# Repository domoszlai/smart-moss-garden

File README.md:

# smart-moss-garden

https://www.youtube.com/watch?v=s0qQqOkIP7w

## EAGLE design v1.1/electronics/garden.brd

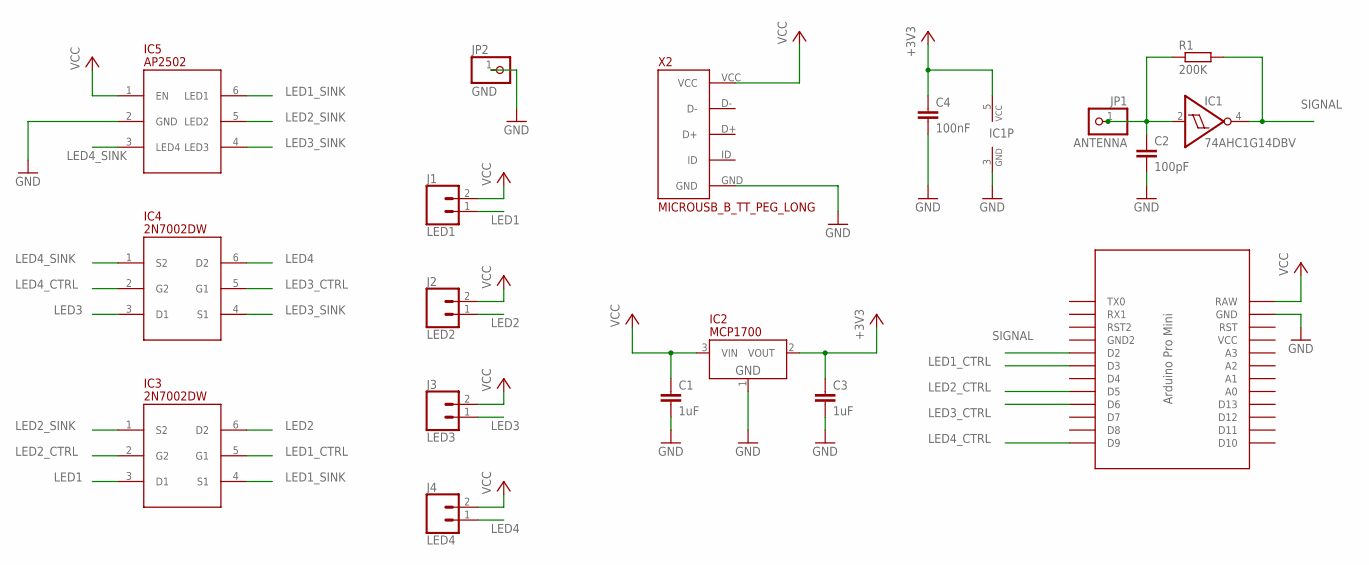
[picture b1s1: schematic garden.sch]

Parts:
C1, C3: 1uF; C0805
C2: 100pF; C0805
C4: 100nF; C0805
IC1: 74AHC1G14DBV; SOT23-5
IC2: MCP1700; SOT-23
IC3, IC4: 2N7002DW; SOT363
IC5: AP2502; SOT-23-6
J1: LED1; 1X02
J2: LED2; 1X02
J3: LED3; 1X02
J4: LED4; 1X02
JP1: ANTENNA; 1X01
JP2: GND; 1X01
R1: 200K; R0805
U$1: PRO-MINI-TWO-SIDES-ONLY
X2: MICROUSB_B_TT_PEG_LONG

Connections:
+3V3: C3.1, C4.1, IC1.5 (VCC), IC2.2 (VOUT)
ANTENNA: C2.1, IC1.2 (I), JP1.1, R1.1
GND: C1.2, C2.2, C3.2, C4.2, IC1.3 (GND), IC2.1 (GND), IC5.2 (GND), JP2.1, U$1.GND, X2.GND
LED1: IC3.3 (D1), J1.1
LED1_CTRL: IC3.5 (G1), U$1.D3
LED1_SINK: IC3.4 (S1), IC5.6 (LED1)
LED2: IC3.6 (D2), J2.1
LED2_CTRL: IC3.2 (G2), U$1.D5
LED2_SINK: IC3.1 (S2), IC5.5 (LED2)
LED3: IC4.3 (D1), J3.1
LED3_CTRL: IC4.5 (G1), U$1.D6
LED3_SINK: IC4.4 (S1), IC5.4 (LED3)
LED4: IC4.6 (D2), J4.1
LED4_CTRL: IC4.2 (G2), U$1.D9
LED4_SINK: IC4.1 (S2), IC5.3 (LED4)
SIGNAL: IC1.4 (O), R1.2, U$1.D2
VCC: C1.1, IC2.3 (VIN), IC5.1 (EN), J1.2, J2.2, J3.2, J4.2, U$1.RAW, X2.VCC

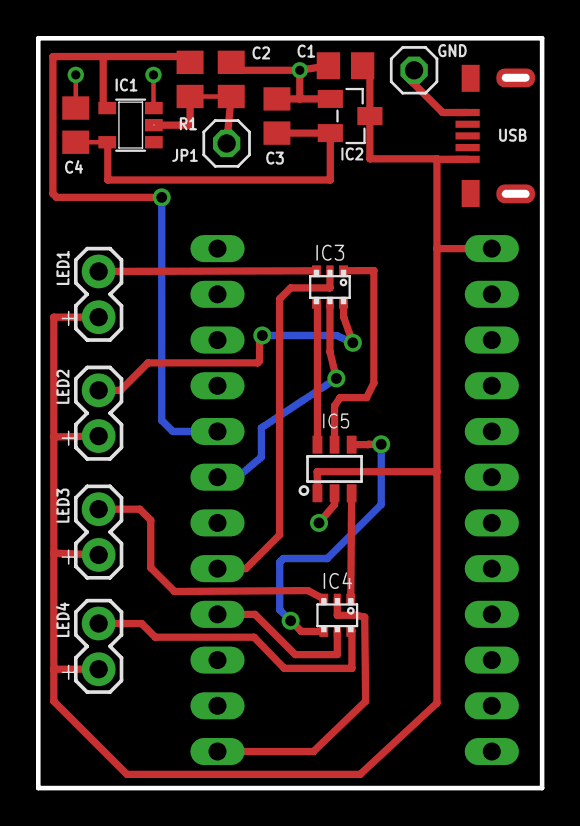
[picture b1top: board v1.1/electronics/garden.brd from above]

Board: 2 copper layers, 27.8 x 41.5 mm, 18 parts (0 on the bottom side), 17 nets.

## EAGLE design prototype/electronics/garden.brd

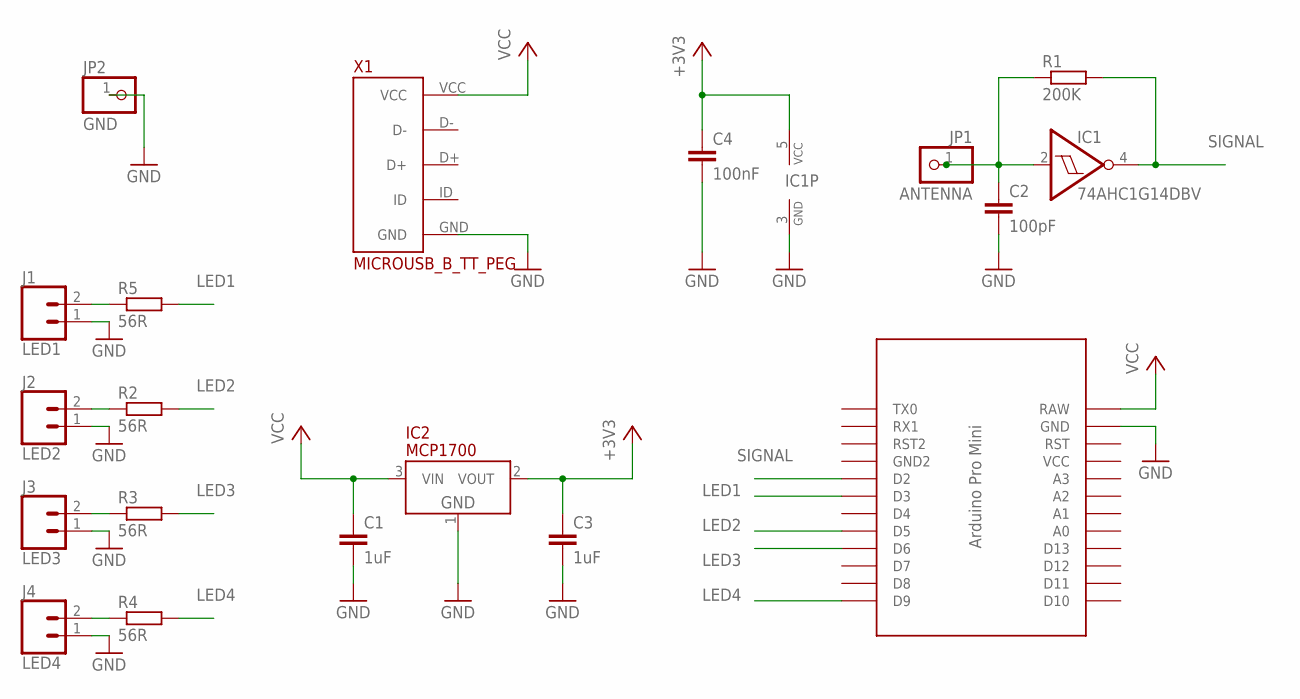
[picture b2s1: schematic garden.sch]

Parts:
C1, C3: 1uF; C0805
C2: 100pF; C0805
C4: 100nF; C0805
IC1: 74AHC1G14DBV; SOT23-5
IC2: MCP1700; SOT-23
J1: LED1; 1X02
J2: LED2; 1X02
J3: LED3; 1X02
J4: LED4; 1X02
JP1: ANTENNA; 1X01
JP2: GND; 1X01
R1: 200K; R0805
R2, R3, R4, R5: 56R; M0805
U$1: PRO-MINI-TWO-SIDES-ONLY
X1: MICROUSB_B_TT_PEG

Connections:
+3V3: C3.1, C4.1, IC1.5 (VCC), IC2.2 (VOUT)
ANTENNA: C2.1, IC1.2 (I), JP1.1, R1.1
GND: C1.2, C2.2, C3.2, C4.2, IC1.3 (GND), IC2.1 (GND), J1.1, J2.1, J3.1, J4.1, JP2.1, U$1.GND, X1.GND
LED1: R5.2, U$1.D3
LED2: R2.2, U$1.D5
LED3: R3.2, U$1.D6
LED4: R4.2, U$1.D9
unnamed: J1.2, R5.1
unnamed: J2.2, R2.1
unnamed: J3.2, R3.1
unnamed: J4.2, R4.1
SIGNAL: IC1.4 (O), R1.2, U$1.D2
VCC: C1.1, IC2.3 (VIN), U$1.RAW, X1.VCC

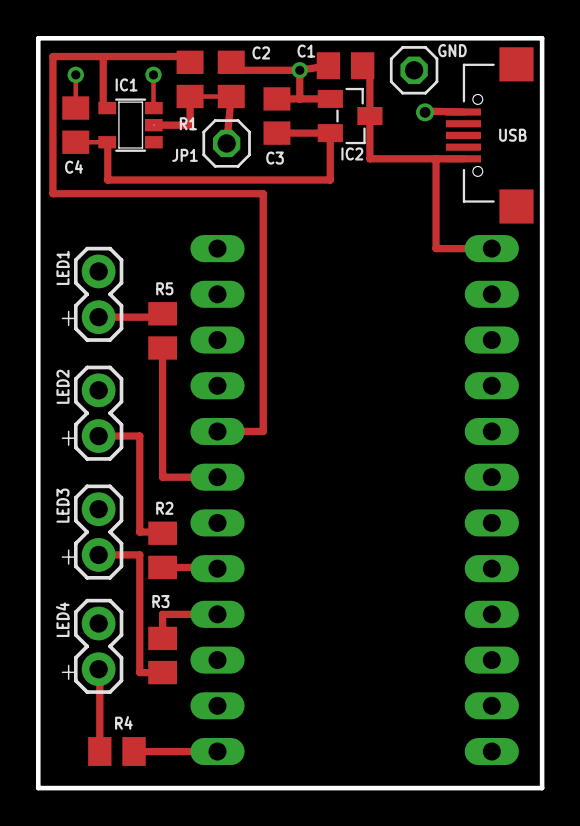
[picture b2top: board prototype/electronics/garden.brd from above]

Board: 2 copper layers, 28.0 x 41.7 mm, 19 parts (0 on the bottom side), 13 nets.

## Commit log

2017-03-25 the electronics design and the firmware for the prototype
2017-03-26 add box design from 2mm/3mm perplex
2017-07-14 1.0 schematics
2017-07-14 fix pinout
2017-08-25 v1.0 board
2017-08-27 ground plane isolation to 12mil
2017-08-27 add gerber files
2017-11-29 add latest electronics
2017-11-29 add schematics as PDF
2017-12-28 Add USB layout
2017-12-28 fix typo
2017-12-28 v1.1
2017-12-28 save progress in development
2017-12-28 remove diy files

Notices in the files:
parts and their libraries:
SparkFun-Connectors: Licensing: Creative Commons ShareAlike 4.0 International - https://creativecommons.org/licenses/by-sa/4.0
